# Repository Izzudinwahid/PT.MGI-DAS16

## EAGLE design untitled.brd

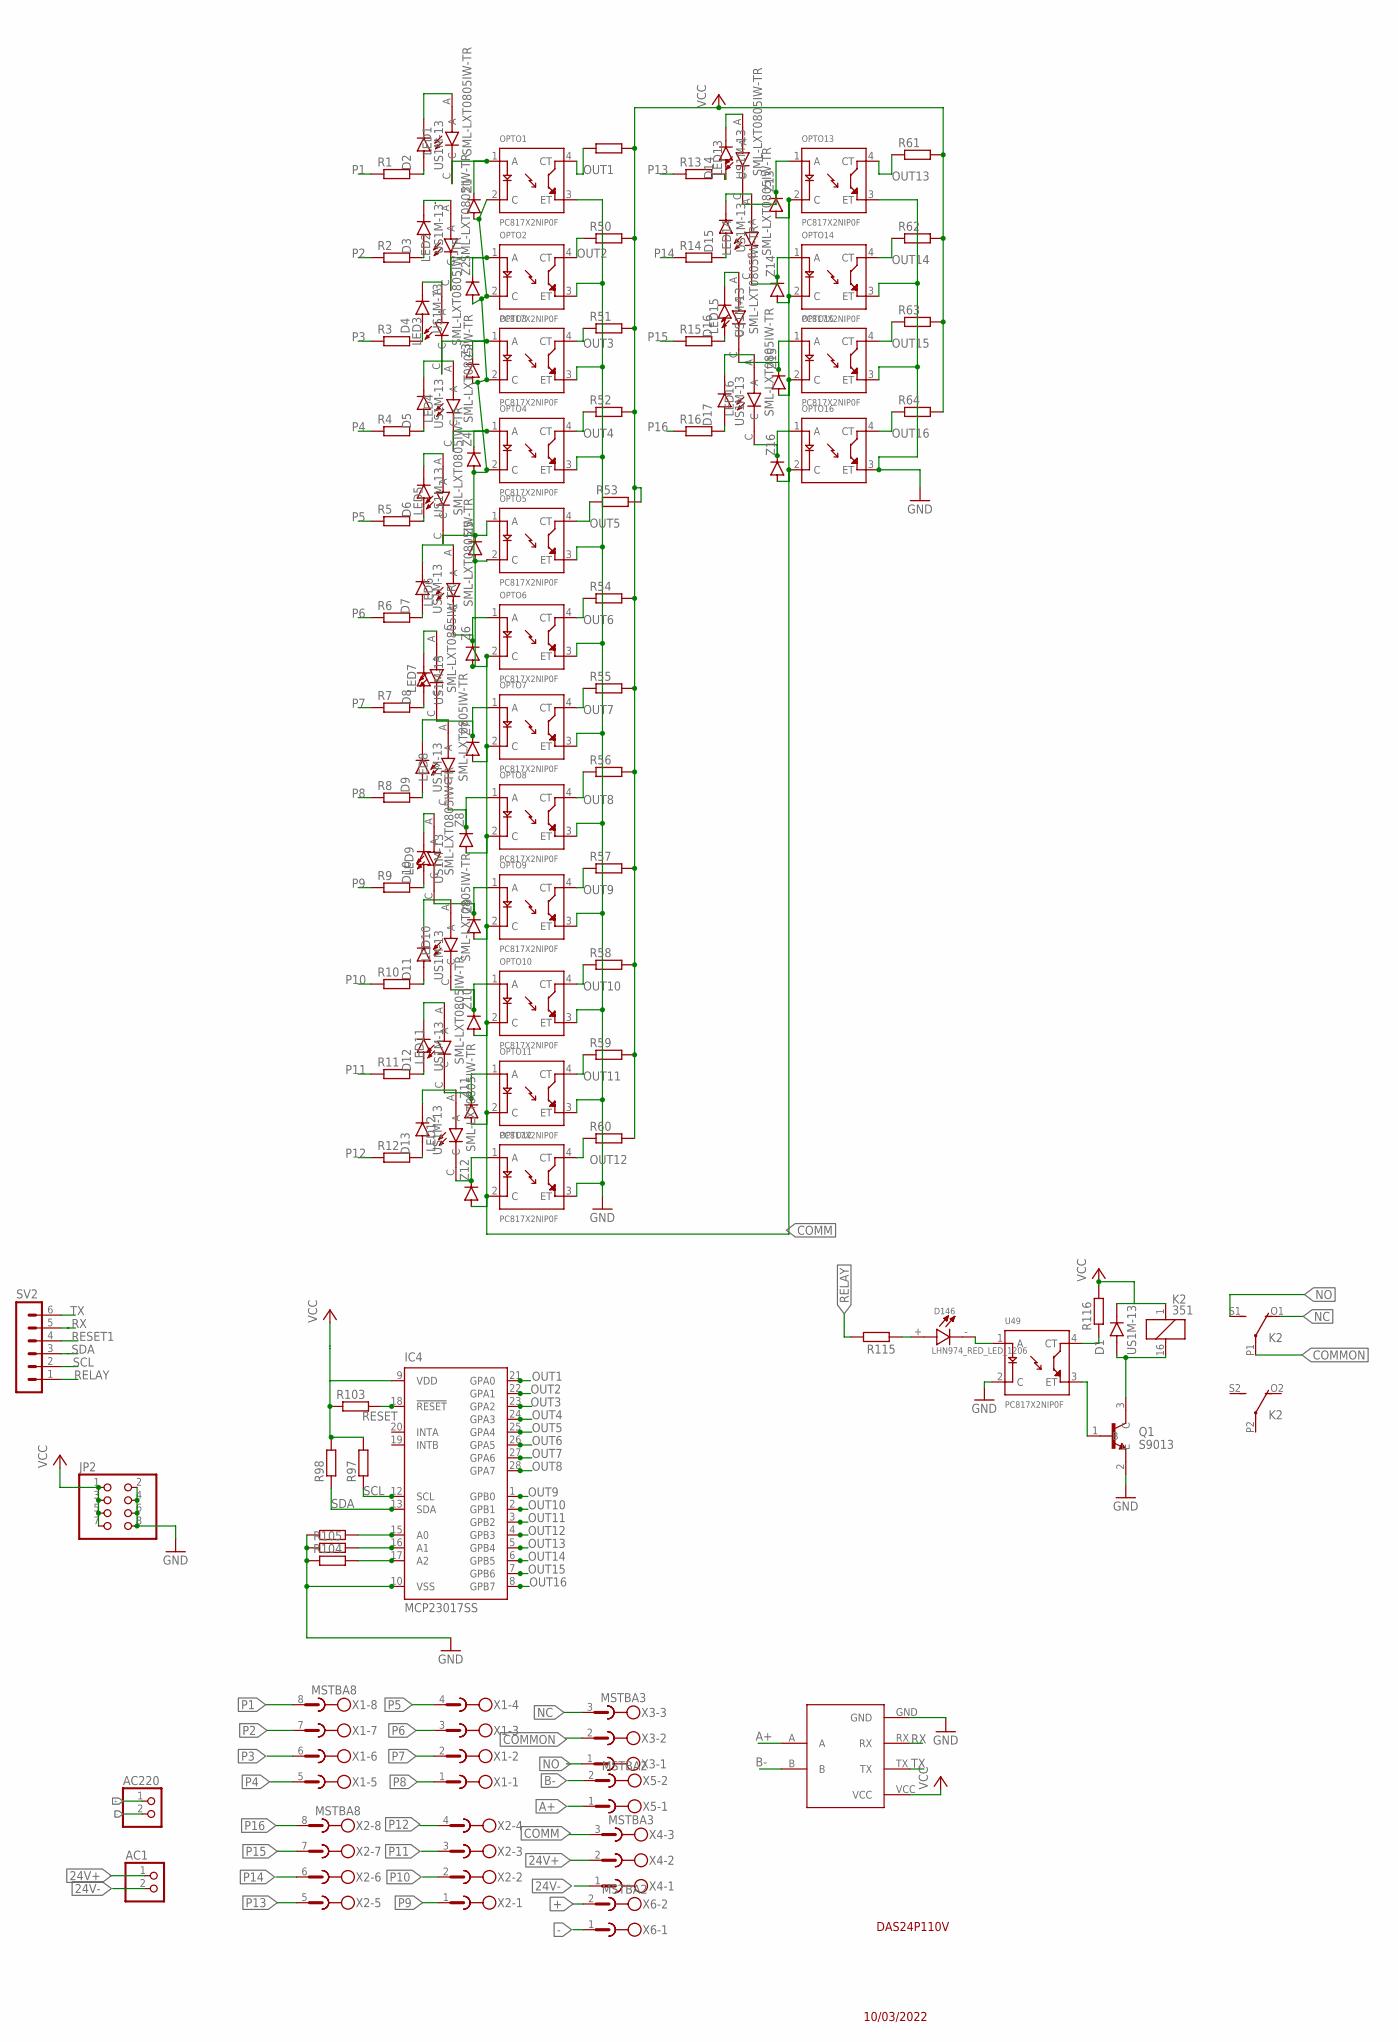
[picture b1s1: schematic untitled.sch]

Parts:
AC1, AC220: PINHD-1X2; 1X02
D1, D2, D3, D4, D5, D6, D7, D8, D9, D10, D11, D12, D13, D14, D15, D16, D17: US1M-13; DIOM5226X240N
D146: LHN974_RED_LED_1206; LEDC3216X120N
IC4: MCP23017SS; SSOP28DB
JP2: PINHD-2X4; 2X04
K2: 351
LED1, LED2, LED3, LED4, LED5, LED6, LED7, LED8, LED9, LED10, LED11, LED12, LED13, LED14, LED15, LED16: SML-LXT0805IW-TR; LEDC2012X120N
OPTO1, OPTO2, OPTO3, OPTO4, OPTO5, OPTO6, OPTO7, OPTO8, OPTO9, OPTO10, OPTO11, OPTO12, OPTO13, OPTO14, OPTO15, OPTO16: PC817X2NIP0F; SOT254P975X400-4N
Q1: S9013; SOT95P240X120-3N
R1, R2, R3, R4, R5, R6, R7, R8, R9, R10, R11, R12, R13, R14, R15, R16: R-EU_0414/15; 0414/15
R49, R50, R51, R52, R53, R54, R55, R56, R57, R58, R59, R60, R61, R62, R63, R64, R97, R98, R103, R104, R105, R106, R115, R116: R-EU_R0805; R0805
SV2: MA06-1
TTL-RS1: TTL-RS485
U49: PC817X2NIP0F; SOT254P975X400-4N
X1, X2: MSTBA8
X3, X4: MSTBA3
X5, X6: MSTBA2
Z1, Z2, Z3, Z4, Z5, Z6, Z7, Z8, Z9, Z10, Z11, Z12, Z13, Z14, Z15, Z16: DIODE-SOD123; SOD123

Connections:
24V+: AC1.1, X4.2
24V-: AC1.2, X4.1
+: AC220.1, X6.2
-: AC220.2, X6.1
A+: TTL-RS1.A, X5.1
B-: TTL-RS1.B, X5.2
COMM: OPTO1.2 (C), OPTO2.2 (C), OPTO3.2 (C), OPTO4.2 (C), OPTO5.2 (C), OPTO6.2 (C), OPTO7.2 (C), OPTO8.2 (C), OPTO9.2 (C), OPTO10.2 (C), OPTO11.2 (C), OPTO12.2 (C), OPTO13.2 (C), OPTO14.2 (C), OPTO15.2 (C), OPTO16.2 (C), X4.3, Z1.A, Z2.A, Z3.A, Z4.A, Z5.A, Z6.A, Z7.A, Z8.A, Z9.A, Z10.A, Z11.A, Z12.A, Z13.A, Z14.A, Z15.A, Z16.A
COMMON: K2.P1, X3.2
GND: IC4.10 (VSS), JP2.2, JP2.4, JP2.6, JP2.8, OPTO1.3 (ET), OPTO2.3 (ET), OPTO3.3 (ET), OPTO4.3 (ET), OPTO5.3 (ET), OPTO6.3 (ET), OPTO7.3 (ET), OPTO8.3 (ET), OPTO9.3 (ET), OPTO10.3 (ET), OPTO11.3 (ET), OPTO12.3 (ET), OPTO13.3 (ET), OPTO14.3 (ET), OPTO15.3 (ET), OPTO16.3 (ET), Q1.2 (E), R104.1, R105.1, R106.1, TTL-RS1.GND, U49.2 (C)
unnamed: D2.A, R1.2
unnamed: LED10.C, OPTO10.1 (A), Z10.C
unnamed: D3.A, R2.2
unnamed: D4.A, R3.2
unnamed: LED1.C, OPTO1.1 (A), Z1.C
unnamed: D5.A, R4.2
unnamed: D2.C (K), LED1.A
unnamed: D6.A, R5.2
unnamed: D3.C (K), LED2.A
unnamed: D7.A, R6.2
unnamed: LED2.C, OPTO2.1 (A), Z2.C
unnamed: D8.A, R7.2
unnamed: D4.C (K), LED3.A
unnamed: D9.A, R8.2
unnamed: LED3.C, OPTO3.1 (A), Z3.C
unnamed: D15.A, R14.2
unnamed: D5.C (K), LED4.A
unnamed: LED4.C, OPTO4.1 (A), Z4.C
unnamed: D10.A, R9.2
unnamed: D6.C (K), LED5.A
unnamed: LED5.C, OPTO5.1 (A), Z5.C
unnamed: D7.C (K), LED6.A
unnamed: D11.A, R10.2
unnamed: D8.C (K), LED7.A
unnamed: LED6.C, OPTO6.1 (A), Z6.C
unnamed: D12.A, R11.2
unnamed: D13.A, R12.2
unnamed: D14.A, R13.2
unnamed: D16.A, R15.2
unnamed: D17.A, R16.2
unnamed: D9.C (K), LED8.A
unnamed: D10.C (K), LED9.A
unnamed: D11.C (K), LED10.A
unnamed: D12.C (K), LED11.A
unnamed: D13.C (K), LED12.A
unnamed: D14.C (K), LED13.A
unnamed: D15.C (K), LED14.A
unnamed: D16.C (K), LED15.A
unnamed: D17.C (K), LED16.A
unnamed: LED7.C, OPTO7.1 (A), Z7.C
unnamed: LED8.C, OPTO8.1 (A), Z8.C
unnamed: LED9.C, OPTO9.1 (A), Z9.C
unnamed: LED11.C, OPTO11.1 (A), Z11.C
unnamed: LED12.C, OPTO12.1 (A), Z12.C
unnamed: LED13.C, OPTO13.1 (A), Z13.C
unnamed: LED14.C, OPTO14.1 (A), Z14.C
unnamed: LED15.C, OPTO15.1 (A), Z15.C
unnamed: LED16.C, OPTO16.1 (A), Z16.C
unnamed: D146.-, U49.1 (A)
unnamed: D146.+, R115.1
unnamed: R116.1, U49.4 (CT)
unnamed: D1.A, K2.16 (2), Q1.3 (C)
unnamed: Q1.1 (B), U49.3 (ET)
unnamed: IC4.15 (A0), R106.2
unnamed: IC4.16 (A1), R105.2
unnamed: IC4.17 (A2), R104.2
NC: K2.O1 (O), X3.3
NO: K2.S1 (S), X3.1
OUT1: IC4.21 (GPA0), OPTO1.4 (CT), R49.1
OUT2: IC4.22 (GPA1), OPTO2.4 (CT), R50.1
OUT3: IC4.23 (GPA2), OPTO3.4 (CT), R51.1
OUT4: IC4.24 (GPA3), OPTO4.4 (CT), R52.1
OUT5: IC4.25 (GPA4), OPTO5.4 (CT), R53.1
OUT6: IC4.26 (GPA5), OPTO6.4 (CT), R54.1
OUT7: IC4.27 (GPA6), OPTO7.4 (CT), R55.1
OUT8: IC4.28 (GPA7), OPTO8.4 (CT), R56.1
OUT9: IC4.1 (GPB0), OPTO9.4 (CT), R57.1
OUT10: IC4.2 (GPB1), OPTO10.4 (CT), R58.1
OUT11: IC4.3 (GPB2), OPTO11.4 (CT), R59.1
OUT12: IC4.4 (GPB3), OPTO12.4 (CT), R60.1
OUT13: IC4.5 (GPB4), OPTO13.4 (CT), R61.1
OUT14: IC4.6 (GPB5), OPTO14.4 (CT), R62.1
OUT15: IC4.7 (GPB6), OPTO15.4 (CT), R63.1
OUT16: IC4.8 (GPB7), OPTO16.4 (CT), R64.1
P1: R1.1, X1.8
P2: R2.1, X1.7
P3: R3.1, X1.6
P4: R4.1, X1.5
P5: R5.1, X1.4
P6: R6.1, X1.3
P7: R7.1, X1.2
P8: R8.1, X1.1
P9: R9.1, X2.1
P10: R10.1, X2.2
P11: R11.1, X2.3
P12: R12.1, X2.4
P13: R13.1, X2.5
P14: R14.1, X2.6
P15: R15.1, X2.7
P16: R16.1, X2.8
RELAY: R115.2, SV2.1
RESET: IC4.18 (!RESET), R103.2
RESET1: SV2.4
RX: SV2.5, TTL-RS1.RX
SCL: IC4.12 (SCL), R97.1, SV2.2
SDA: IC4.13 (SDA), R98.1, SV2.3
TX: SV2.6, TTL-RS1.TX
VCC: D1.C (K), IC4.9 (VDD), JP2.1, JP2.3, JP2.5, JP2.7, K2.1, R49.2, R50.2, R51.2, R52.2, R53.2, R54.2, R55.2, R56.2, R57.2, R58.2, R59.2, R60.2, R61.2, R62.2, R63.2, R64.2, R97.2, R98.2, R103.1, R116.2, TTL-RS1.VCC

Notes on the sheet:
DAS24P110V
10/03/2022

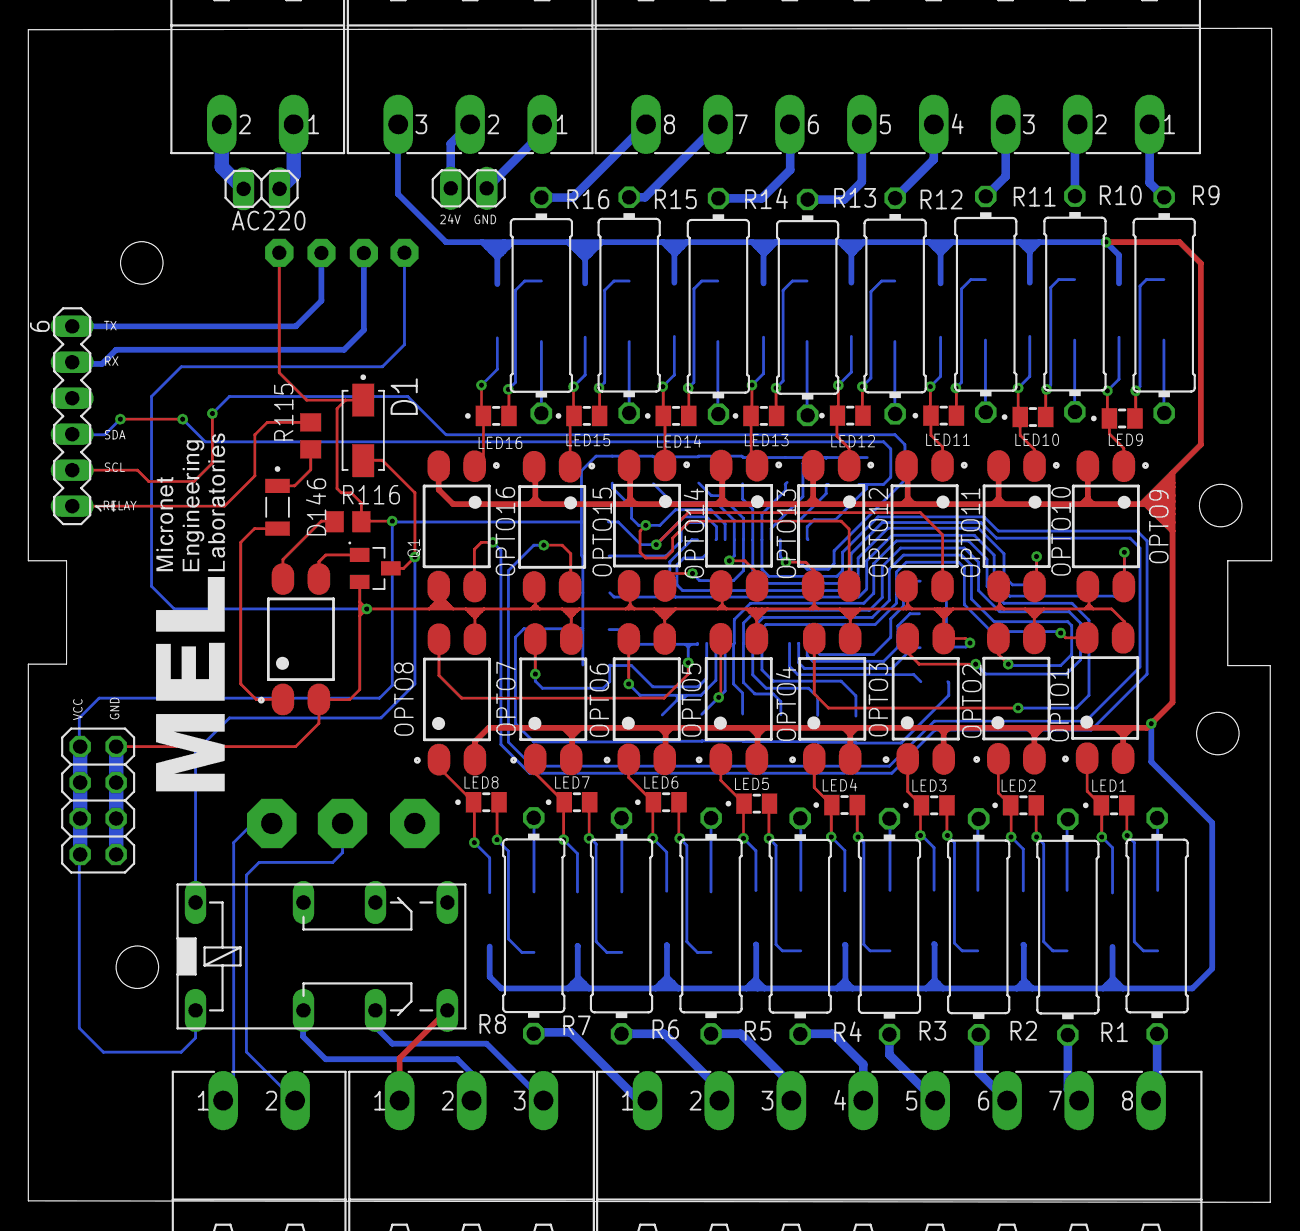
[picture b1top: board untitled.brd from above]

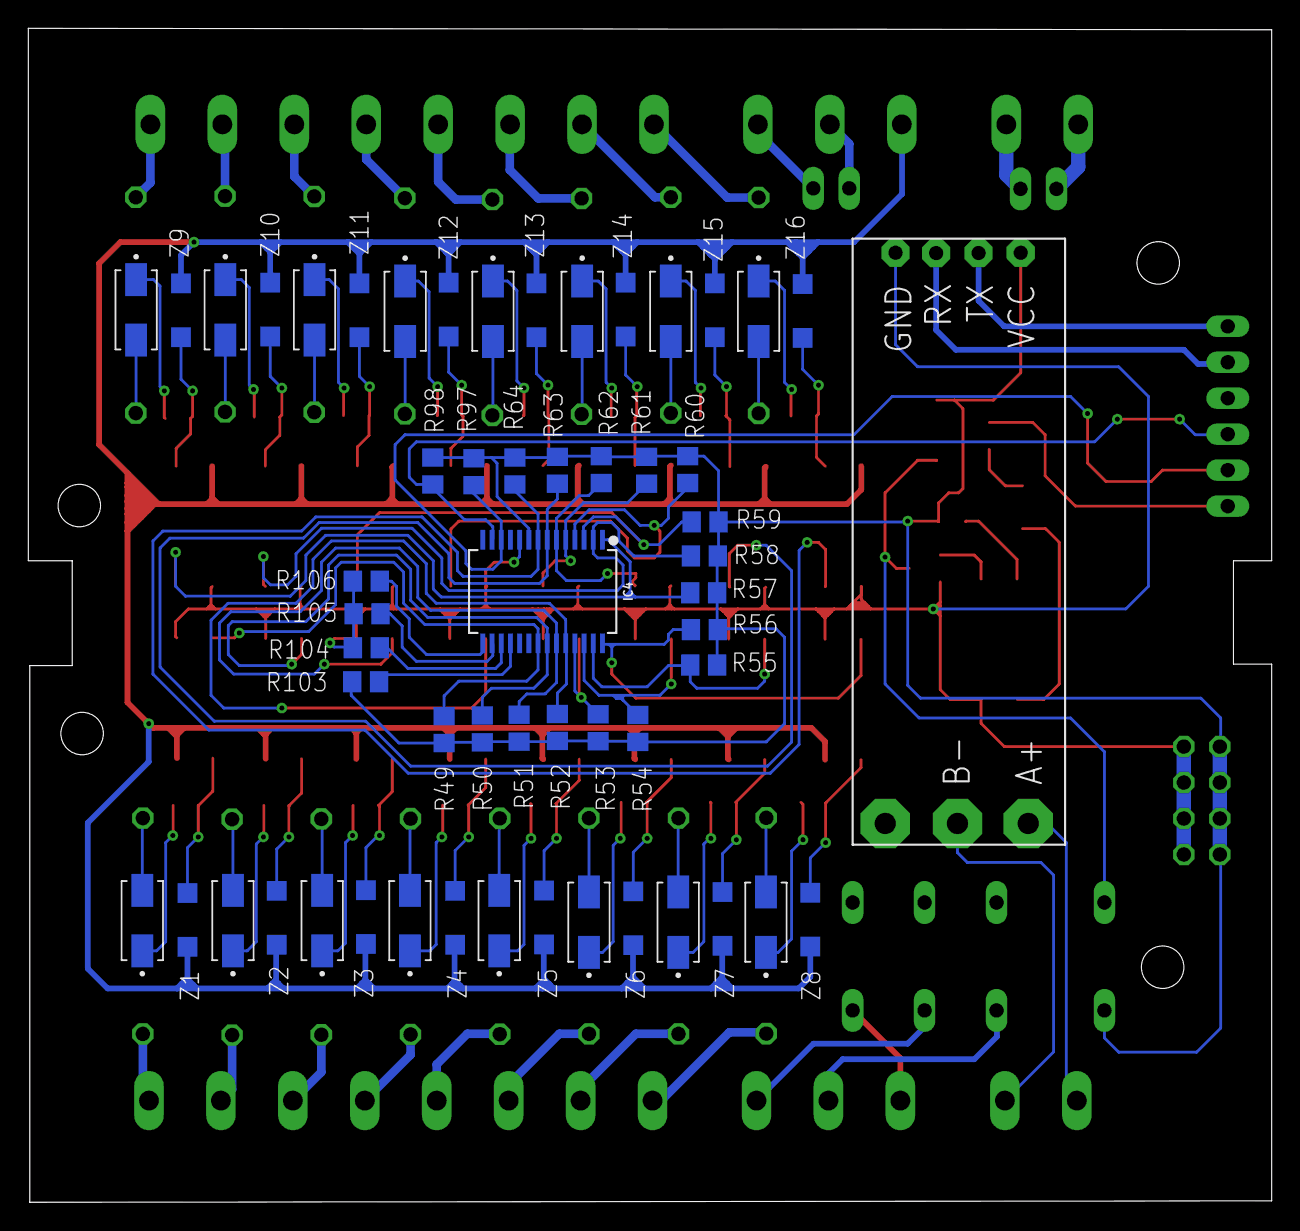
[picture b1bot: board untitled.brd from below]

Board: 2 copper layers, 87.8 x 82.9 mm, 121 parts (56 on the bottom side), 106 nets.

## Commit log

2022-08-10 menambahkan File .sch
2022-08-10 membuat file .brd
2022-08-11 revisi PCB
2022-08-12 revisi logo
2022-08-12 revisi board
2022-08-12 revisi .brd
